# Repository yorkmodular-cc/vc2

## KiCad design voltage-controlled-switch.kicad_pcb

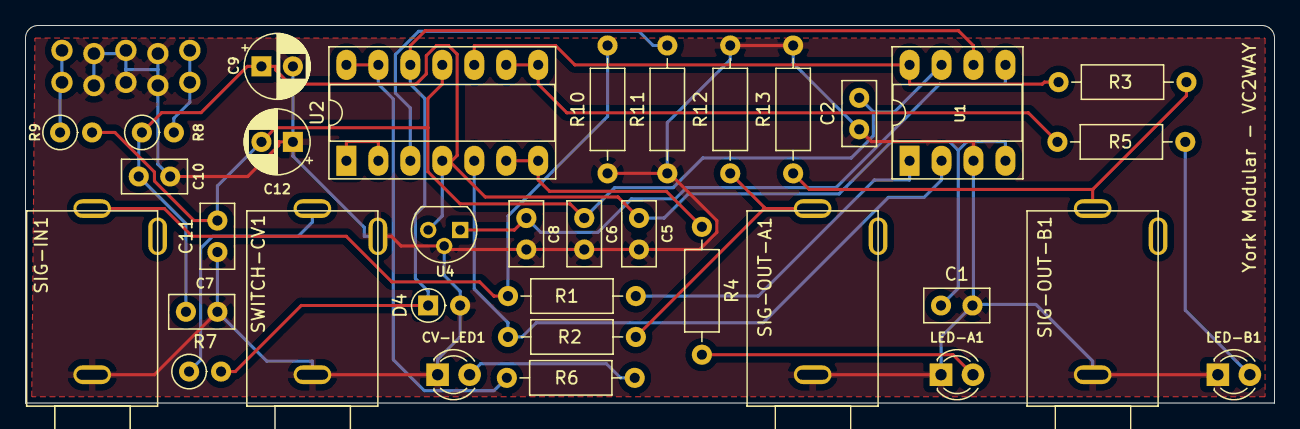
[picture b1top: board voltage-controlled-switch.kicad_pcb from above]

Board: 2 copper layers, 99.2 x 30.0 mm, 35 parts (1 on the bottom side), 22 nets.

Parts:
C1, C2, C5, C6, C7, C8, C10, C11: 100n; C_Disc_D5.0mm_W2.5mm_P2.50mm
C9, C12: 10u; CP_Radial_D5.0mm_P2.50mm
CV-LED1: LED; LED_D3.0mm
D4: D_Zener_ALT; D_DO-35_SOD27_P2.54mm_Vertical_AnodeUp
J1: EURO_PWR_2x5; EURO-POWER
LED-A1: LED_Dual_2pin; LED_D3.0mm
LED-B1: LED_Dual_2pin; LED_D3.0mm
R1, R2, R3: 1k; R_Axial_DIN0207_L6.3mm_D2.5mm_P10.16mm_Horizontal
R4, R5, R6: 10k; R_Axial_DIN0207_L6.3mm_D2.5mm_P10.16mm_Horizontal
R7: 1k; R_Axial_DIN0207_L6.3mm_D2.5mm_P2.54mm_Vertical
R8, R9: 22R; R_Axial_DIN0207_L6.3mm_D2.5mm_P2.54mm_Vertical
R10, R11, R12, R13: 100k; R_Axial_DIN0207_L6.3mm_D2.5mm_P10.16mm_Horizontal
SIG-IN1: PJ301M-12; PJ302m
SIG-OUT-A1: PJ301M-12; PJ302m
SIG-OUT-B1: PJ301M-12; PJ302m
SWITCH-CV1: PJ301M-12; PJ302m
U1: DG419LDJ; DIP-8_W7.62mm_Socket_LongPads
U2: TL074; DIP-14_W7.62mm_Socket_LongPads
U4: 7805_PINS; TO-92

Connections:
+5V: C8.1, U1.5, U4.1
+12V: C1.1, C5.2, C7.1, C9.1, C10.1, R8.1, U1.4, U2.4, U4.3
-12V: C2.2, C6.2, C11.2, C12.2, R9.2, U1.7, U2.11
GND: C1.2, C2.1, C5.1, C6.1, C7.2, C8.2, C9.2, C10.2, C11.1, C12.1, CV-LED1.1, D4.2, J1.3, J1.4, J1.5, J1.6, J1.7, J1.8, LED-A1.1, LED-B1.1, R10.1, R11.1, R12.2, R13.2, SIG-IN1.1, SIG-OUT-A1.1, SIG-OUT-B1.1, SWITCH-CV1.1, SWITCH-CV1.2, U1.3, U4.2
unnamed: CV-LED1.2, R6.2
unnamed: J1.1, J1.2, R8.2
unnamed: J1.9, J1.10, R9.1
unnamed: LED-A1.2, R4.2
unnamed: LED-B1.2, R5.2
unnamed: R1.2, R10.2, SIG-IN1.3
unnamed: R4.1, U2.6, U2.7
unnamed: R5.1, U2.8, U2.9
unnamed: R6.1, U2.13, U2.14
unnamed: R7.1, SWITCH-CV1.3
unnamed: R11.2, U2.3
unnamed: R2.1, R12.1, SIG-OUT-A1.3
unnamed: R3.1, R13.1, SIG-OUT-B1.3
unnamed: U2.1, U2.2
SIG1-IN: R1.1, U1.1
SW1-A: R2.2, U1.2, U2.5
SW1-B: R3.2, U1.8, U2.10
SW-CV-1: D4.1, R7.2, U1.6, U2.12

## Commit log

2022-05-22 Create LICENSE
